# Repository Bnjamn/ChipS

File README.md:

# ChipS
ChipS, The PSX Modchip Support

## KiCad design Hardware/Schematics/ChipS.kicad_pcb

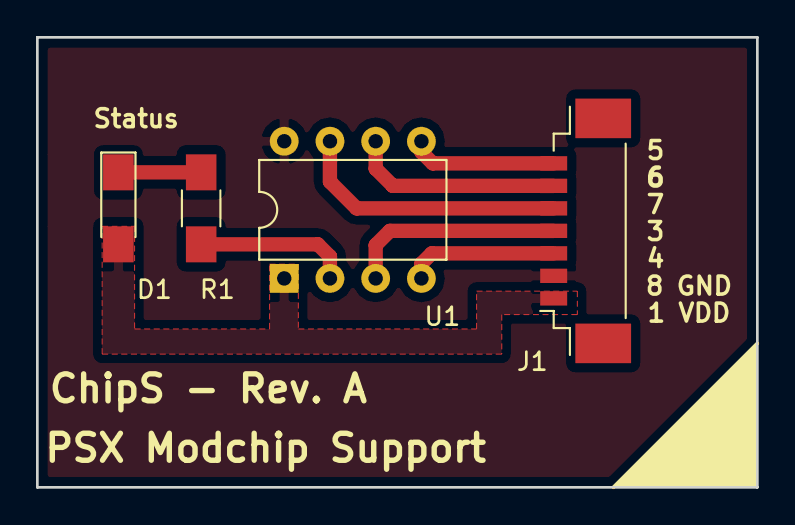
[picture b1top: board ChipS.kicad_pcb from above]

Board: 2 copper layers, 40.0 x 25.0 mm, 4 parts (0 on the bottom side), 9 nets.

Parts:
D1: LED; LED_1206_HandSoldering
J1: CONN_01X07; Molex_PicoBlade_53398-0771_07x1.25mm_Straight
R1: 120R; R_1206_HandSoldering
U1: PIC12C508; DIP-8_W7.62mm

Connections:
/GP0: J1.5, U1.7
/GP1: J1.6, U1.6
/GP2: J1.7, U1.5
/GP3: J1.3, U1.4
/GP4: J1.4, U1.3
/GP5: R1.2, U1.2
GND: J1.2, U1.8
unnamed: D1.1, R1.1
VDD: D1.2, J1.1, U1.1

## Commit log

2017-07-26 Add files via upload
    First Hardware Commit
2017-07-26 Add files via upload
    First Documentation Repository Upload
2017-07-29 Add files via upload
    ChipS 30_07_2017 Update
2017-10-19 Add files via upload
    2nd hardware commit
